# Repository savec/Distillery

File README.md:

# Distillery
Distillery automatization

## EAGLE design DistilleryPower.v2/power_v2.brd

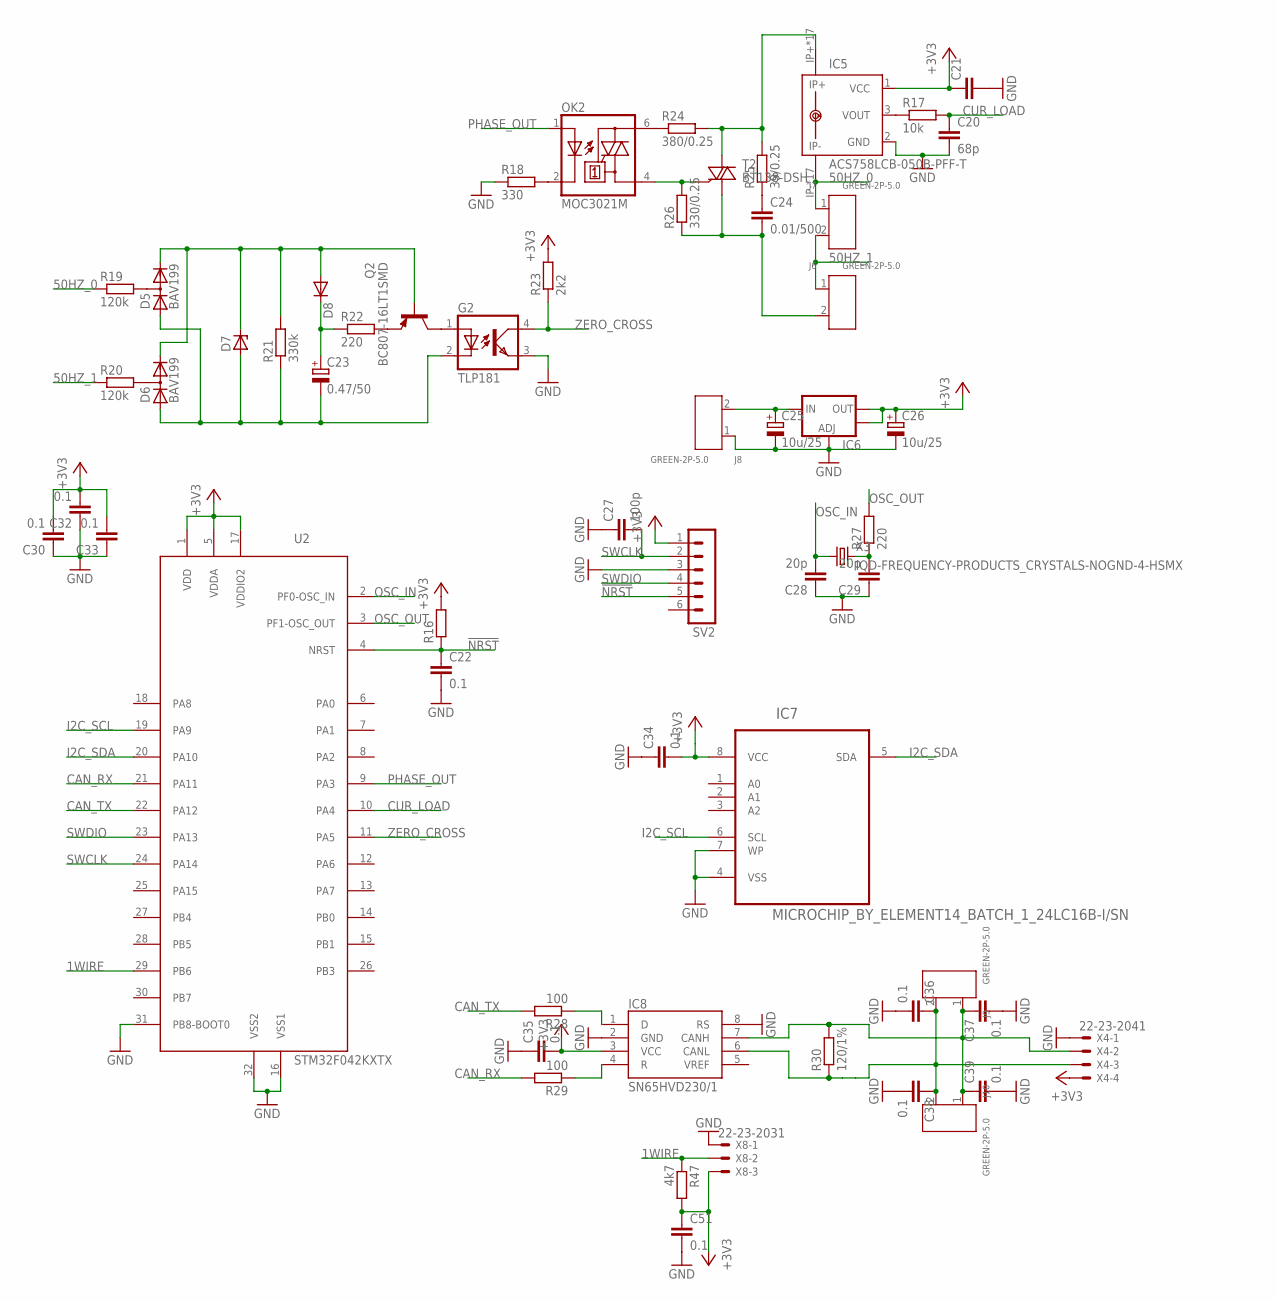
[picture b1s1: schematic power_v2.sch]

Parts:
C20: 68p; C0603
C21: C-EUC0603; C0603
C22, C30, C32, C33, C34, C35, C36, C37, C38, C39, C51: 0.1; C0603
C23: 0.47/50; C/6032-28R
C24: 0.01/500; C1206
C25, C26: 10u/25; SMC_B
C27: 100p; C0603
C28, C29: 20p; C0603
D5, D6: BAV199; SOT23
D7: ZENER-DIODESOD80C; SOD80C
D8: DIODE-SOD523; SOD523
G2: TLP181; SOP04
IC5: ACS758LCB-050B-PFF-T; CB-PFF
IC6: V_REG_LM1117SOT223; SOT223
IC7: MICROCHIP_BY_ELEMENT14_BATCH_1_24LC16B-I/SN; MICROCHIP_BY_ELEMENT14_BATCH_1_SOIC127P600X175-8N
IC8: SN65HVD230/1; SO8
J6, J7, J8, J9, J10: GREEN-2P-5.0; H2-5.0-10.5X8.0MM
OK2: MOC3021M; DIL06
Q2: BC807-16LT1SMD; SOT23-BEC
R16: R-EU_R0603; R0603
R17: 10k; R0603
R18: 330; R0603
R19, R20: 120k; R1206
R21: 330k; R1206
R22: 220; R1206
R23: 2k2; R0603
R24: 380/0.25; M1206
R25: 39/0.25; M1206
R26: 330/0.25; M1206
R27: 220; R0603
R28, R29: 100; R0603
R30: 120/1%; R0603
R47: 4k7; R0603
SV2: CON-LSTB_MA06-1
T2: BT138-DSH; TO220DSH
U2: STM32F042KXTX; LQFP32
X3: IQD-FREQUENCY-PRODUCTS_CRYSTALS-NOGND-4-HSMX; IQD-FREQUENCY-PRODUCTS_HC49-4-HSMX
X4: 22-23-2041
X8: 22-23-2031

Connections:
1WIRE: R47.1, U2.29 (PB6), X8.2
50HZ_0: IC5.IP-, IC5.IP-@2 (IP-), IC5.IP-@3 (IP-), IC5.IP-@4 (IP-), IC5.IP-@5 (IP-), IC5.IP-@6 (IP-), IC5.IP-@7 (IP-), IC5.IP-@8 (IP-), IC5.IP-@9 (IP-), IC5.IP-@10 (IP-), IC5.IP-@11 (IP-), IC5.IP-@12 (IP-), IC5.IP-@13 (IP-), IC5.IP-@14 (IP-), IC5.IP-@15 (IP-), IC5.IP-@16 (IP-), IC5.IP-@17 (IP-), J7.1, R19.1
50HZ_1: J6.1, J7.2, R20.1
!NRST: C22.1, R16.1, SV2.5, U2.4 (NRST)
+3V3: C21.1, C26.+, C30.2, C32.2, C33.2, C34.2, C35.2, C51.1, IC5.1 (VCC), IC6.2 (OUT), IC6.4 (OUT), IC7.8 (VCC), IC8.3 (VCC), R16.2, R23.2, R47.2, SV2.1, U2.1 (VDD), U2.5 (VDDA), U2.17 (VDDIO2), X4.4, X8.3
CAN_RX: R29.2, U2.21 (PA11)
CAN_TX: R28.2, U2.22 (PA12)
CUR_LOAD: C20.1, R17.2, U2.10 (PA4)
GND: C20.2, C21.2, C22.2, C25.-, C26.-, C27.1, C28.1, C29.1, C30.1, C32.1, C33.1, C34.1, C35.1, C36.2, C37.2, C38.2, C39.2, C51.2, G2.3 (EMIT), IC5.2 (GND), IC6.1 (ADJ), IC7.4 (VSS), IC7.7 (WP), IC8.2 (GND), IC8.8 (RS), J8.1, R18.1, SV2.3, U2.16 (VSS1), U2.31 (PB8-BOOT0), U2.32 (VSS2), X4.1, X8.1
I2C_SCL: IC7.6 (SCL), U2.19 (PA9)
I2C_SDA: IC7.5 (SDA), U2.20 (PA10)
unnamed: IC5.3 (VOUT), R17.1
unnamed: D5.3 (AC), R19.2
unnamed: D6.3 (AC), R20.2
unnamed: D5.2 (C), D6.2 (C), D7.C, D8.A, Q2.B, R21.2
unnamed: C23.-, D5.1 (A), D6.1 (A), D7.A, G2.2 (C), R21.1
unnamed: C23.+, D8.C, R22.1
unnamed: Q2.E, R22.2
unnamed: G2.1 (A), Q2.C
unnamed: OK2.6 (A2), R24.1
unnamed: C24.1, R25.1
unnamed: OK2.4 (A1), R26.2, T2.G
unnamed: IC5.IP+, IC5.IP+@2 (IP+), IC5.IP+@3 (IP+), IC5.IP+@4 (IP+), IC5.IP+@5 (IP+), IC5.IP+@6 (IP+), IC5.IP+@7 (IP+), IC5.IP+@8 (IP+), IC5.IP+@9 (IP+), IC5.IP+@10 (IP+), IC5.IP+@11 (IP+), IC5.IP+@12 (IP+), IC5.IP+@13 (IP+), IC5.IP+@14 (IP+), IC5.IP+@15 (IP+), IC5.IP+@16 (IP+), IC5.IP+@17 (IP+), R24.2, R25.2, T2.A2
unnamed: C24.2, J6.2, R26.1, T2.A1
unnamed: C25.+, IC6.3 (IN), J8.2
unnamed: C29.2, R27.1, X3.2
unnamed: C36.1, C38.1, IC8.6 (CANL), J9.2, J10.2, R30.1, X4.3
unnamed: IC8.1 (D), R28.1
unnamed: IC8.4 (R), R29.1
unnamed: C37.1, C39.1, IC8.7 (CANH), J9.1, J10.1, R30.2, X4.2
unnamed: OK2.2 (C), R18.2
OSC_IN: C28.2, U2.2 (PF0-OSC_IN), X3.1
OSC_OUT: R27.2, U2.3 (PF1-OSC_OUT)
PHASE_OUT: OK2.1 (A), U2.9 (PA3)
SWCLK: C27.2, SV2.2, U2.24 (PA14)
SWDIO: SV2.4, U2.23 (PA13)
ZERO_CROSS: G2.4 (COL), R23.1, U2.11 (PA5)

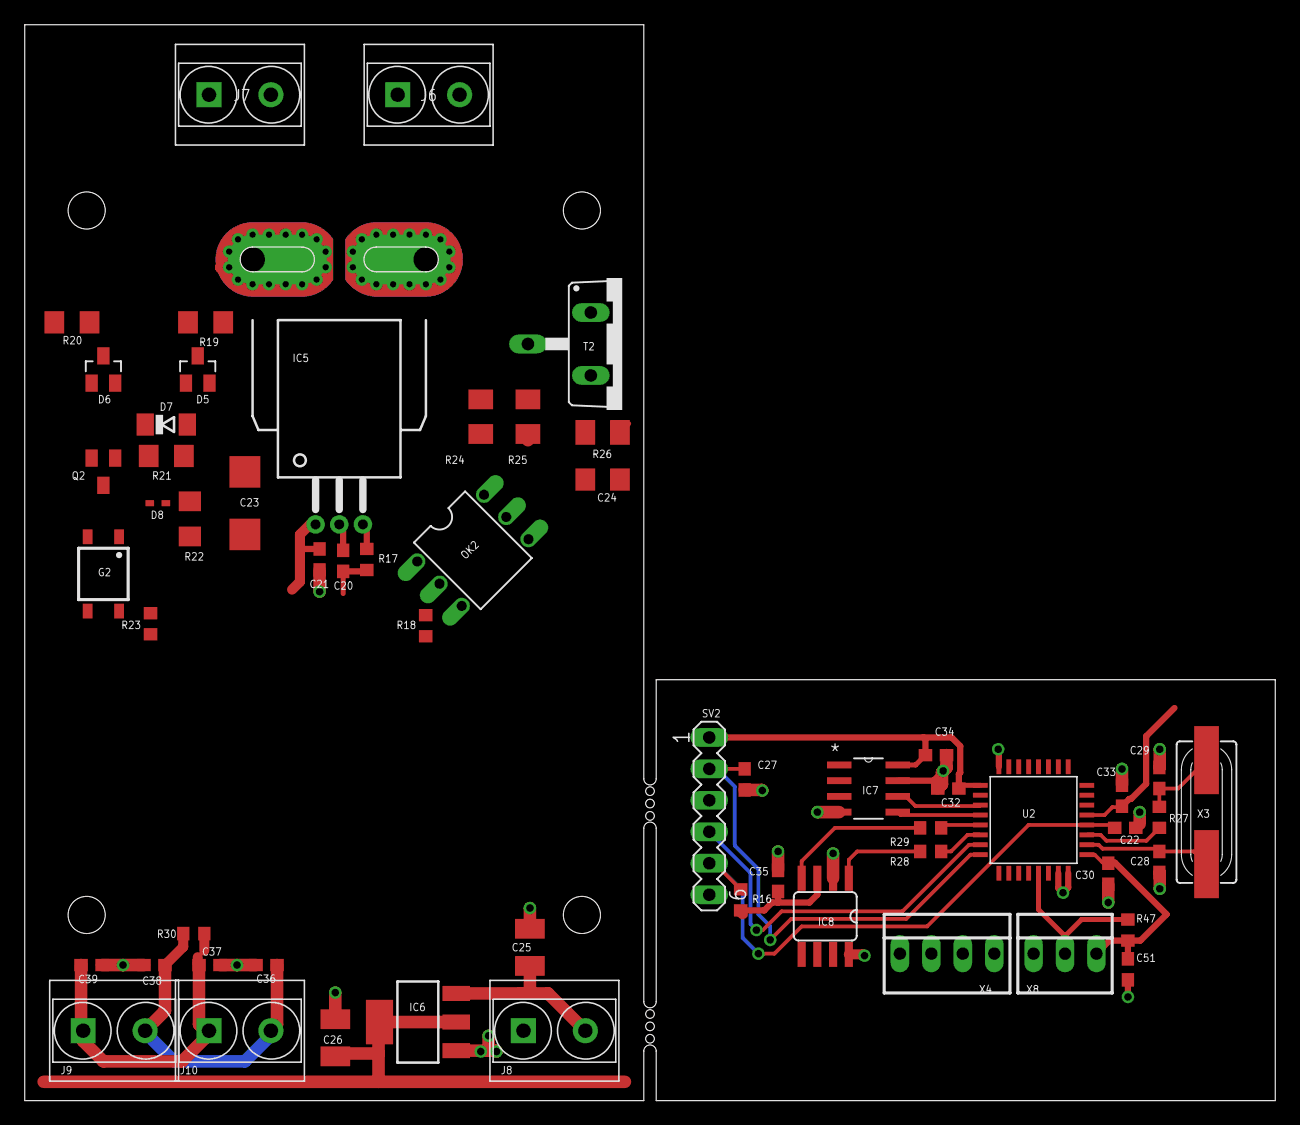
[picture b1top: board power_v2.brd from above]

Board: 2 copper layers, 101.0 x 86.9 mm, 58 parts (0 on the bottom side), 37 nets.

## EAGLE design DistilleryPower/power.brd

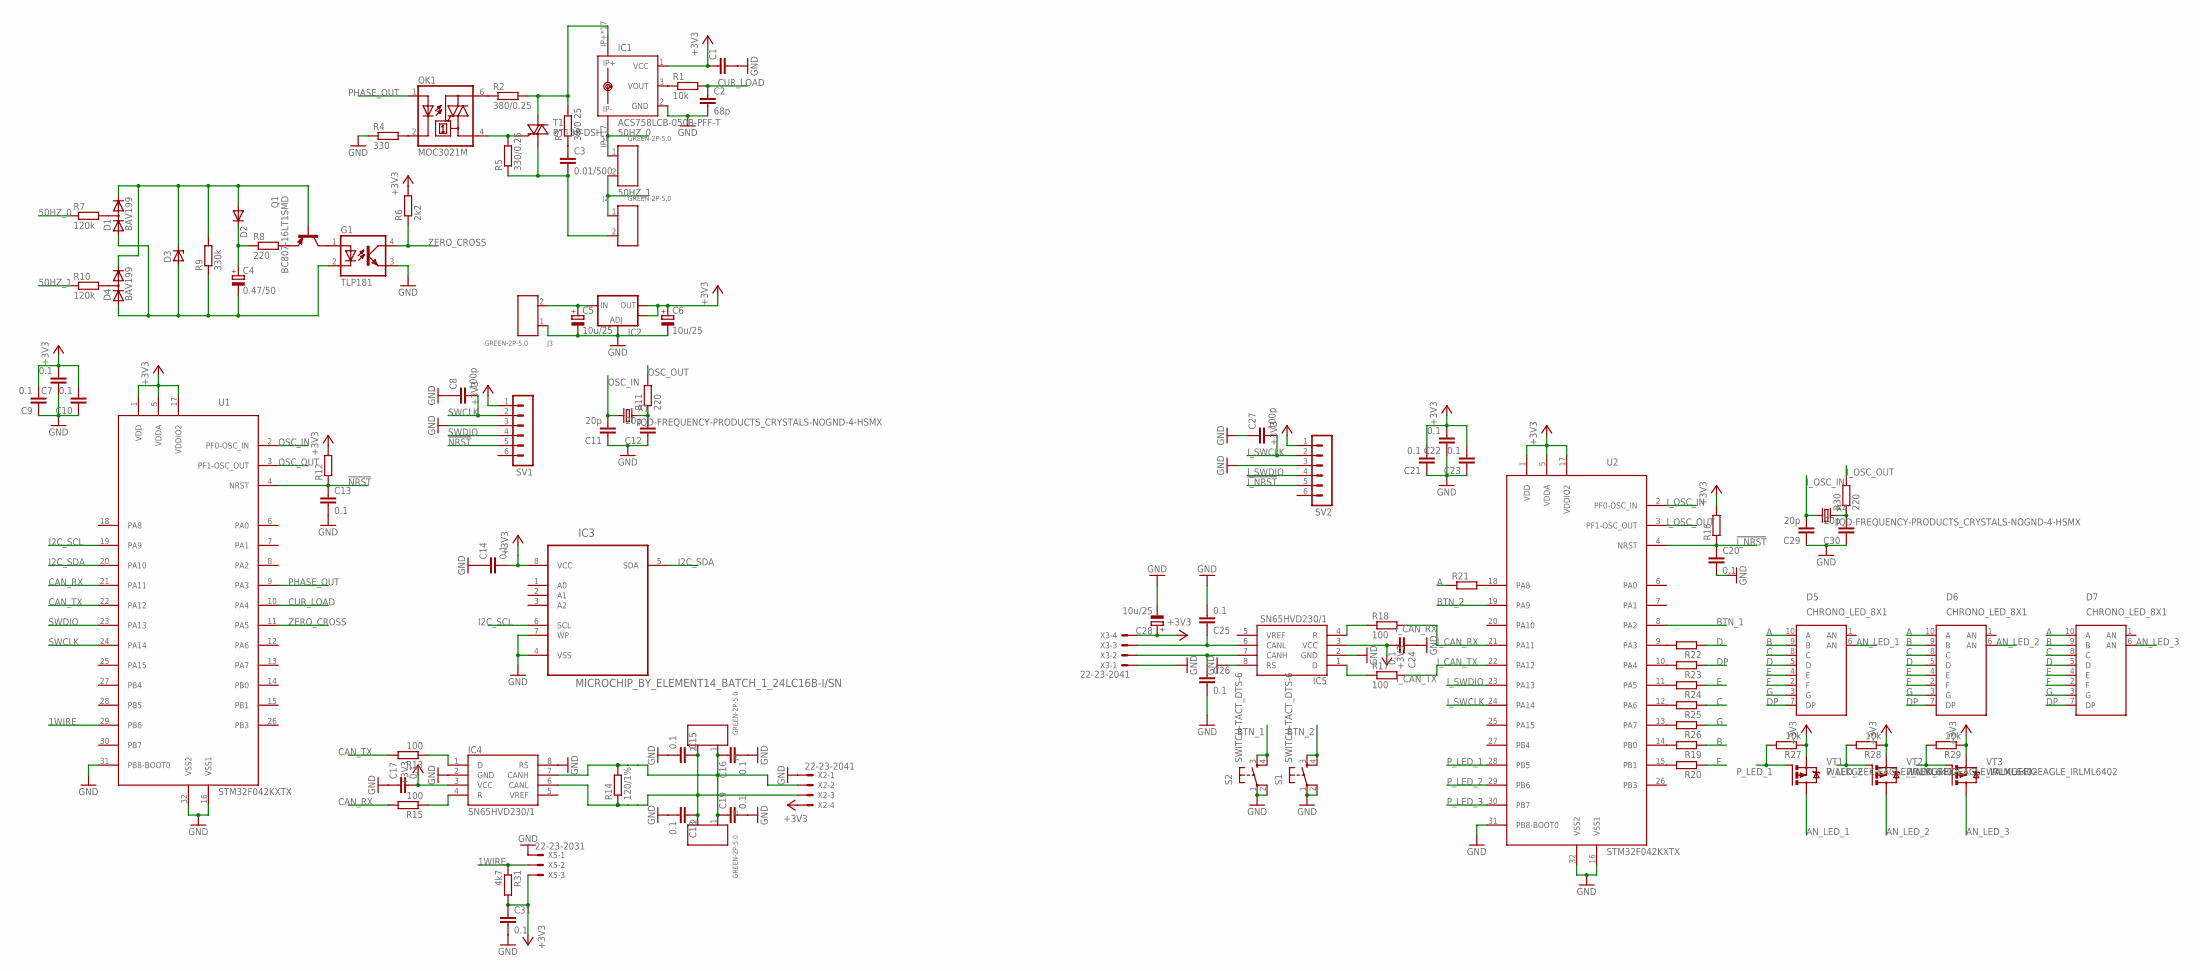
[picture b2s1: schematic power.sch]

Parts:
C1: C-EUC0603; C0603
C2: 68p; C0603
C3: 0.01/500; C1206
C4: 0.47/50; C/6032-28R
C5, C6, C28: 10u/25; SMC_B
C7, C9, C10, C13, C14, C15, C16, C17, C18, C19, C20, C21, C22, C23, C24, C25, C26, C31: 0.1; C0603
C8, C27: 100p; C0603
C11, C12, C29, C30: 20p; C0603
D1, D4: BAV199; SOT23
D2: DIODE-SOD523; SOD523
D3: ZENER-DIODESOD80C; SOD80C
D5, D6, D7: CHRONO_LED_8X1; CHRONO_LED_DIP10
G1: TLP181; SOP04
IC1: ACS758LCB-050B-PFF-T; CB-PFF
IC2: V_REG_LM1117SOT223; SOT223
IC3: MICROCHIP_BY_ELEMENT14_BATCH_1_24LC16B-I/SN; MICROCHIP_BY_ELEMENT14_BATCH_1_SOIC127P600X175-8N
IC4, IC5: SN65HVD230/1; SO8
J1, J2, J3, J4, J5: GREEN-2P-5.0; H2-5.0-10.5X8.0MM
OK1: MOC3021M; DIL06
Q1: BC807-16LT1SMD; SOT23-BEC
R1, R27, R28, R29: 10k; R0603
R2: 380/0.25; M1206
R3: 39/0.25; M1206
R4: 330; R0603
R5: 330/0.25; M1206
R6: 2k2; R0603
R7, R10: 120k; R1206
R8: 220; R1206
R9: 330k; R1206
R11, R30: 220; R0603
R12, R16, R19, R20, R21, R22, R23, R24, R25, R26: R-EU_R0603; R0603
R13, R15, R17, R18: 100; R0603
R14: 120/1%; R0603
R31: 4k7; R0603
S1, S2: SWITCH-TACT_DTS-6
SV1, SV2: CON-LSTB_MA06-1
T1: BT138-DSH; TO220DSH
U1, U2: STM32F042KXTX; LQFP32
VT1, VT2, VT3: WALKGEEK-EAGLE_IRLML6402; WALKGEEK-EAGLE_MICRO3
X1, X4: IQD-FREQUENCY-PRODUCTS_CRYSTALS-NOGND-4-HSMX; IQD-FREQUENCY-PRODUCTS_HC49-4-HSMX
X2, X3: 22-23-2041
X5: 22-23-2031

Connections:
1WIRE: R31.1, U1.29 (PB6), X5.2
50HZ_0: IC1.IP-, IC1.IP-@2 (IP-), IC1.IP-@3 (IP-), IC1.IP-@4 (IP-), IC1.IP-@5 (IP-), IC1.IP-@6 (IP-), IC1.IP-@7 (IP-), IC1.IP-@8 (IP-), IC1.IP-@9 (IP-), IC1.IP-@10 (IP-), IC1.IP-@11 (IP-), IC1.IP-@12 (IP-), IC1.IP-@13 (IP-), IC1.IP-@14 (IP-), IC1.IP-@15 (IP-), IC1.IP-@16 (IP-), IC1.IP-@17 (IP-), J1.1, R7.1
50HZ_1: J1.2, J2.1, R10.1
!I_NRST: C20.1, R16.1, SV2.5, U2.4 (NRST)
!NRST: C13.1, R12.1, SV1.5, U1.4 (NRST)
+3V3: C1.1, C6.+, C7.2, C9.2, C10.2, C14.2, C17.2, C31.1, IC1.1 (VCC), IC2.2 (OUT), IC2.4 (OUT), IC3.8 (VCC), IC4.3 (VCC), R6.2, R12.2, R31.2, SV1.1, U1.1 (VDD), U1.5 (VDDA), U1.17 (VDDIO2), X2.4, X5.3
A: D5.10 (A), D6.10 (A), D7.10 (A), R21.1
AN_LED_1: D5.6 (AN), VT1.3 (D)
AN_LED_2: D6.6 (AN), VT2.3 (D)
AN_LED_3: D7.6 (AN), VT3.3 (D)
B: D5.9 (B), D6.9 (B), D7.9 (B), R19.1
BTN_1: S2.3, S2.4, U2.8 (PA2)
BTN_2: S1.3, S1.4, U2.19 (PA9)
C: D5.8 (C), D6.8 (C), D7.8 (C), R25.1
CAN_RX: R15.2, U1.21 (PA11)
CAN_TX: R13.2, U1.22 (PA12)
CUR_LOAD: C2.1, R1.2, U1.10 (PA4)
D: D5.5 (D), D6.5 (D), D7.5 (D), R22.1
DP: D5.7 (DP), D6.7 (DP), D7.7 (DP), R23.1
E: D5.4 (E), D6.4 (E), D7.4 (E), R24.1
F: D5.2 (F), D6.2 (F), D7.2 (F), R20.1
G: D5.3 (G), D6.3 (G), D7.3 (G), R26.1
GND: C1.2, C2.2, C5.-, C6.-, C7.1, C8.1, C9.1, C10.1, C11.1, C12.1, C13.2, C14.1, C15.2, C16.2, C17.1, C18.2, C19.2, C31.2, G1.3 (EMIT), IC1.2 (GND), IC2.1 (ADJ), IC3.4 (VSS), IC3.7 (WP), IC4.2 (GND), IC4.8 (RS), J3.1, R4.1, SV1.3, U1.16 (VSS1), U1.31 (PB8-BOOT0), U1.32 (VSS2), X2.1, X5.1
I2C_SCL: IC3.6 (SCL), U1.19 (PA9)
I2C_SDA: IC3.5 (SDA), U1.20 (PA10)
I_3V3: C21.2, C22.2, C23.2, C24.2, C28.+, IC5.3 (VCC), R16.2, R27.1, R28.1, R29.1, SV2.1, U2.1 (VDD), U2.5 (VDDA), U2.17 (VDDIO2), VT1.2 (S), VT2.2 (S), VT3.2 (S), X3.4
I_CAN_RX: R18.2, U2.21 (PA11)
I_CAN_TX: R17.2, U2.22 (PA12)
I_GND: C20.2, C21.1, C22.1, C23.1, C24.1, C25.2, C26.2, C27.1, C28.-, C29.1, C30.1, IC5.2 (GND), IC5.8 (RS), S1.1, S1.2, S2.1, S2.2, SV2.3, U2.16 (VSS1), U2.31 (PB8-BOOT0), U2.32 (VSS2), X3.1
I_OSC_IN: C29.2, U2.2 (PF0-OSC_IN), X4.1
I_OSC_OUT: R30.2, U2.3 (PF1-OSC_OUT)
I_SWCLK: C27.2, SV2.2, U2.24 (PA14)
I_SWDIO: SV2.4, U2.23 (PA13)
unnamed: D1.3 (AC), R7.2
unnamed: IC1.3 (VOUT), R1.1
unnamed: D4.3 (AC), R10.2
unnamed: D1.2 (C), D2.A, D3.C, D4.2 (C), Q1.B, R9.2
unnamed: C4.-, D1.1 (A), D3.A, D4.1 (A), G1.2 (C), R9.1
unnamed: C4.+, D2.C, R8.1
unnamed: Q1.E, R8.2
unnamed: G1.1 (A), Q1.C
unnamed: OK1.6 (A2), R2.1
unnamed: C3.1, R3.1
unnamed: OK1.4 (A1), R5.2, T1.G
unnamed: C25.1, IC5.6 (CANL), X3.3
unnamed: C5.+, IC2.3 (IN), J3.2
unnamed: OK1.2 (C), R4.2
unnamed: IC5.1 (D), R17.1
unnamed: C12.2, R11.1, X1.2
unnamed: IC1.IP+, IC1.IP+@2 (IP+), IC1.IP+@3 (IP+), IC1.IP+@4 (IP+), IC1.IP+@5 (IP+), IC1.IP+@6 (IP+), IC1.IP+@7 (IP+), IC1.IP+@8 (IP+), IC1.IP+@9 (IP+), IC1.IP+@10 (IP+), IC1.IP+@11 (IP+), IC1.IP+@12 (IP+), IC1.IP+@13 (IP+), IC1.IP+@14 (IP+), IC1.IP+@15 (IP+), IC1.IP+@16 (IP+), IC1.IP+@17 (IP+), R2.2, R3.2, T1.A2
unnamed: C3.2, J2.2, R5.1, T1.A1
unnamed: IC5.4 (R), R18.1
unnamed: C15.1, C18.1, IC4.6 (CANL), J4.2, J5.2, R14.1, X2.3
unnamed: IC4.1 (D), R13.1
unnamed: IC4.4 (R), R15.1
unnamed: C26.1, IC5.7 (CANH), X3.2
unnamed: C16.1, C19.1, IC4.7 (CANH), J4.1, J5.1, R14.2, X2.2
unnamed: R19.2, U2.14 (PB0)
unnamed: R20.2, U2.15 (PB1)
unnamed: R21.2, U2.18 (PA8)
unnamed: R22.2, U2.9 (PA3)
unnamed: R23.2, U2.10 (PA4)
unnamed: R24.2, U2.11 (PA5)
unnamed: R25.2, U2.12 (PA6)
unnamed: R26.2, U2.13 (PA7)
unnamed: C30.2, R30.1, X4.2
OSC_IN: C11.2, U1.2 (PF0-OSC_IN), X1.1
OSC_OUT: R11.2, U1.3 (PF1-OSC_OUT)
PHASE_OUT: OK1.1 (A), U1.9 (PA3)
P_LED_1: R27.2, U2.28 (PB5), VT1.1 (G)
P_LED_2: R28.2, U2.29 (PB6), VT2.1 (G)
P_LED_3: R29.2, U2.30 (PB7), VT3.1 (G)
SWCLK: C8.2, SV1.2, U1.24 (PA14)
SWDIO: SV1.4, U1.23 (PA13)
ZERO_CROSS: G1.4 (COL), R6.1, U1.11 (PA5)

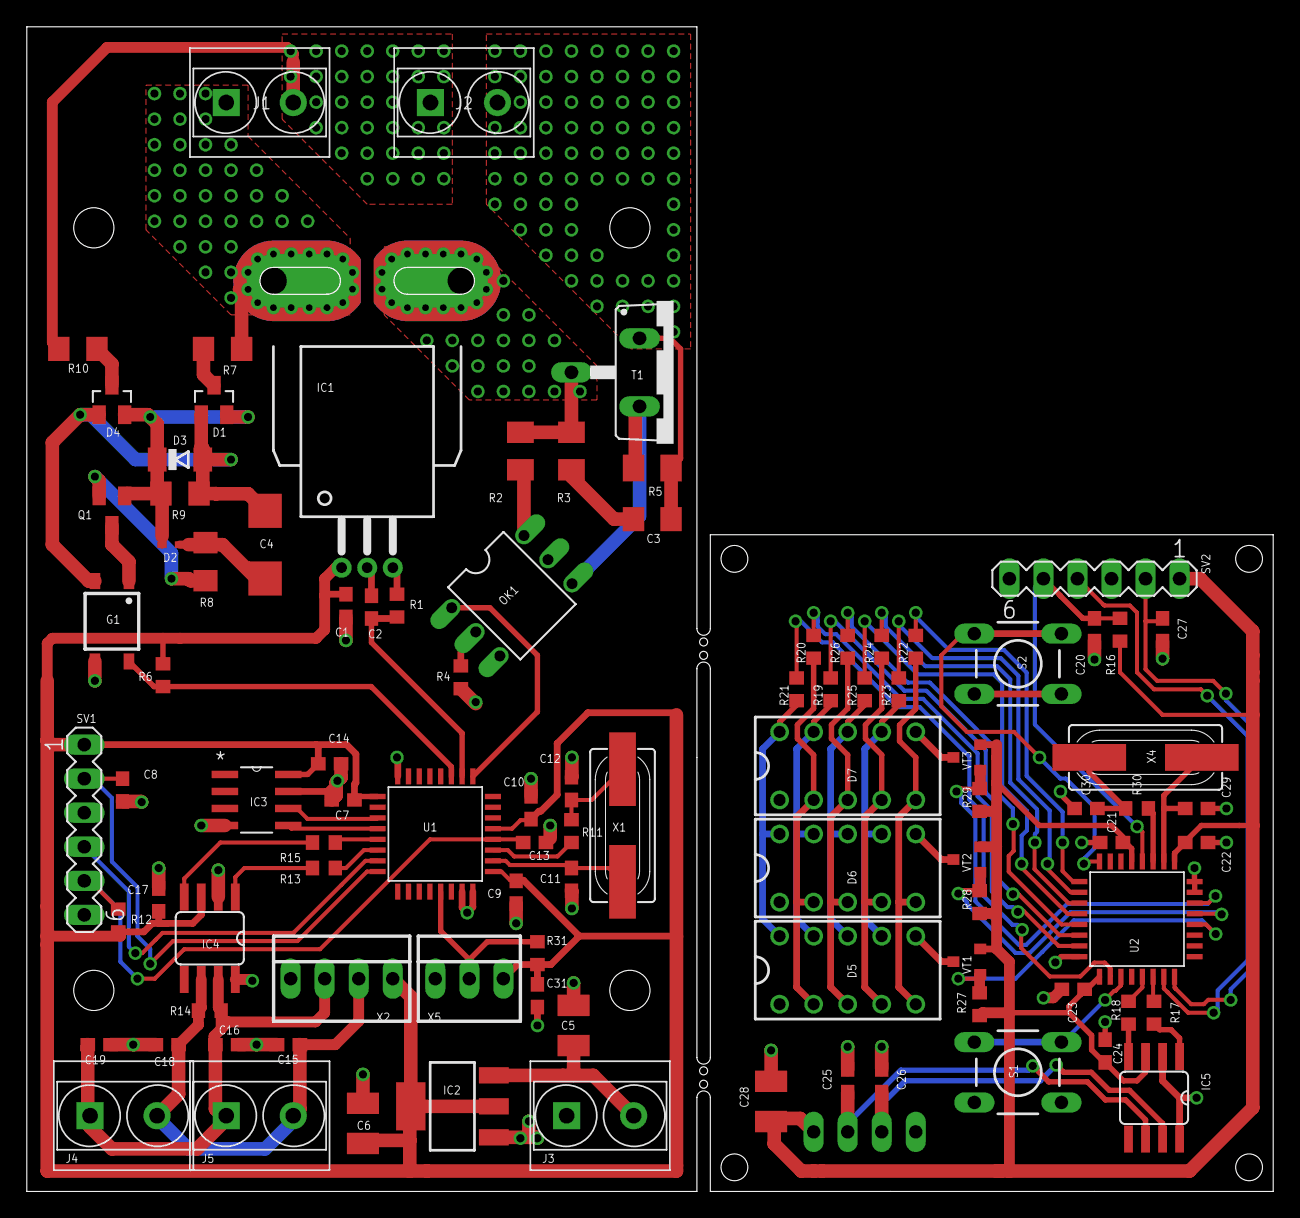
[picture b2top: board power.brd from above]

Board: 2 copper layers, 93.0 x 86.9 mm, 97 parts (1 on the bottom side), 75 nets.

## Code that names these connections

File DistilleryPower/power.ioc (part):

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Mcu.Name=STM32F042K(4-6)Tx
Mcu.Package=LQFP32
Mcu.UserName=STM32F042K6Tx
PA10.Mode=I2C
PA10.Signal=I2C1_SDA
PA11.Mode=Master
PA11.Signal=CAN_RX
PA12.Mode=Master
PA12.Signal=CAN_TX
PA13.Mode=Serial_Wire
PA13.Signal=SYS_SWDIO
PA14.Mode=Serial_Wire
PA14.Signal=SYS_SWCLK
PA3.Signal=S_TIM2_CH4
PA4.Mode=IN4
PA4.Signal=ADC_IN4
PA5.Signal=S_TIM2_CH1_ETR
PA9.Mode=I2C
PA9.Signal=I2C1_SCL
PB6.Signal=USART1_TX
PF0-OSC_IN.Mode=HSE-External-Oscillator
PF0-OSC_IN.Signal=RCC_OSC_IN
PF1-OSC_OUT.Mode=HSE-External-Oscillator
PF1-OSC_OUT.Signal=RCC_OSC_OUT
RCC.SYSCLKFreq_VALUE=48000000
RCC.SYSCLKSource=RCC_SYSCLKSOURCE_PLLCLK
board=custom

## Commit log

2018-08-10 start routing
2018-08-10 digital part schematics
2018-08-12 power control board routing finished
2018-08-14 export all to local library; renumber symbols;
2018-08-14 gerber output
2018-08-15 reroute: indication board with CAN controller
2018-08-16 indication board routing finished
2018-09-11 added 1wire; finished profile layer
2018-09-12 fixed profile
2018-09-14 fixed CAM settings
2018-12-10 design of power board v2 started
2018-12-11 fixed merge

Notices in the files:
parts and their libraries:
SparkFun: Licensing: CC v3.0 Share-Alike You are welcome to use this library for commercial purposes.
